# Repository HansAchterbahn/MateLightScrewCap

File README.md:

# MateLight-ScrewCap
This Repo is based on the idea of [MateLight](http://matelight.rocks/) and improves it by a screw cap which is easy to install and easy to remove from the coasters.

In this Repository you can find
- PCB schematics and board layouts created in Eagle,
- PCB Gerber data (ready for manufacturing),
- a 3D model of the PCB and
- a 3D model of the screw cap (for 3D printer).

Have also a look to the following Repos with Python Code for our MateLight for use with a Raspberry Pi:
- https://git.cccgoe.de/jugendgruppe/matelight-effects
- https://git.cccgoe.de/jugendgruppe/matelight
- https://git.cccgoe.de/jugendgruppe/ml_simulator

A small presentation about the PCB assembly process can be found here:
- https://jugendgruppe.cccgoe.de/reveal_js/00-MateLightScrewCapSoldering.html
- https://jugendgruppe.cccgoe.de/projekte/matelight.html

*Fork me and have fun!*

**MateLight of CCC youth group Göttingen at the 36c3 event 2019 in Leipzig**

## Power source

An APA102C LED consumes a maximum of 60 mA (red/green/blue each 20 mA). It is recommended to use a new 5 V / 1.4 mA power source for each 20 bottles(higher current delivery does not matter).

```
  ___  ^ 5V /    LED 1                            LED 19             LED 20             ___  ^ 5V /   LED 21
   |   | 1.4A  ___________  +5V            +5V   ___________  +5V    ___________ +5V     |   | 1.4A  ___________  +5V
   |   °------|    ___    |------         ------|    ___    |------|    ___    |--|      |   °------|    ___    |------
   |     GND  |   /   \   | GND            GND  |   /   \   | GND  |   /   \   | GND     |     GND  |   /   \   | GND
---°----------|  |     |  |------         ------|  |     |  |------|  |     |  |---------°----------|  |     |  |------
         CLK  |  |     |  | CLK     ...    CLK  |  |     |  | CLK  |  |     |  | CLK           CLK  |  |     |  | CLK     ...
------->------|  |     |  |------         ------|  |     |  |------|  |     |  |------------->------|  |     |  |------
         D    |   \___/   | D              D    |   \___/   | D    |   \___/   | D             D    |   \___/   | D
------->------|___________|------         ------|___________|------|___________|------------->------|___________|------
```

## 3D View (Fusion360)

Animated 3D STL model: [3d-model/MateLightScrewCap.stl](https://github.com/HansAchterbahn/MateLightScrewCap/blob/master/3d-model/MateLightScrewCap.stl)

__Top view__

__Bottom view__

## Schematic

## Board

__Top view__

__Bottom view__

## Manufacturing and assembly

__Manufactured PCBs__

__PCB with Cable__

__Manufactured screw caps__

__Assembled Mate bottle with PCB and screw cap__

__Assembled Mate bottle with PCB and screw cap lighting red__

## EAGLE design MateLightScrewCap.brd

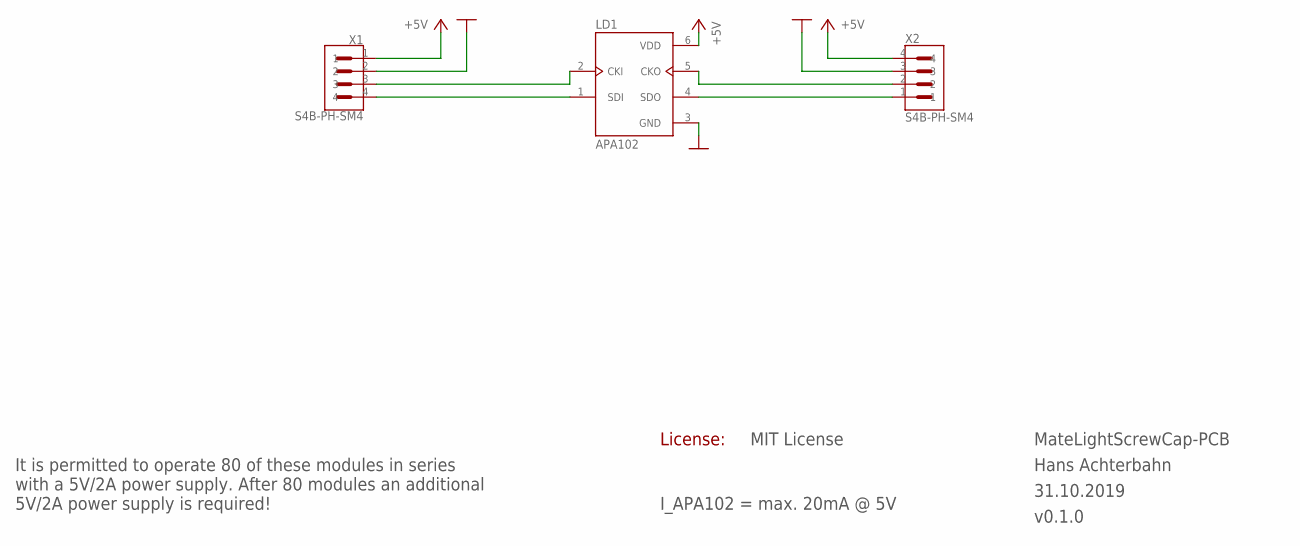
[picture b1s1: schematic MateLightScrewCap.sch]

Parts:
LD1: APA102; APA102C-5050
X1, X2: S4B-PH-SM4; JST_S4B-PH-SM4-TB

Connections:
+5V: LD1.6 (VDD), X1.1, X2.4
GND: LD1.3 (GND), X1.2, X2.3
LED-SPI-CLK-IN: LD1.2 (CKI), X1.3
LED-SPI-CLK-OUT: LD1.5 (CKO), X2.2
LED-SPI-MOSI-IN: LD1.1 (SDI), X1.4
LED-SPI-MOSI-OUT: LD1.4 (SDO), X2.1

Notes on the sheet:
I_APA102 = max. 20mA @ 5V
License:
It is permitted to operate 80 of these modules in series with a 5V/2A power supply. After 80 modules an additional 5V/2A power supply is required!

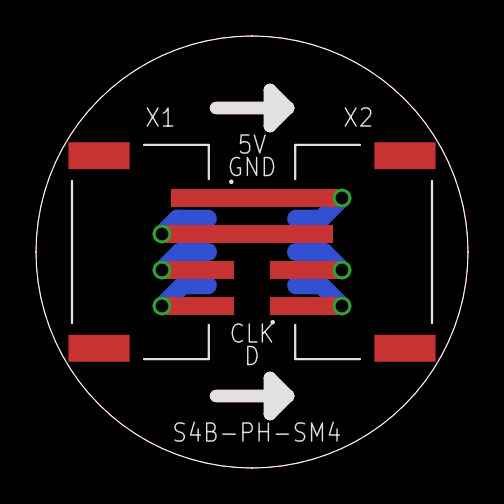
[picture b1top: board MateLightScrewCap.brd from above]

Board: 2 copper layers, 24.0 x 24.0 mm, 3 parts (1 on the bottom side), 6 nets.

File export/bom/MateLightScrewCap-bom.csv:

"Qty";"Value";"Device";"Package";"Parts";"Description";"DESCRIPTION";"DIGI-KEY";"MF";"MFN";"MOUSER";"RS-ONLINE";
"1";"APA102";"APA102APA102C-5050";"APA102C-5050";"LD1";"DotStar Micro LEDs (APA102–2020)- Smart SMD RGB LED - 100 pack";"";"";"";"";"";"";
"2";"S4B-PH-SM4";"S4B-PH-SM4-TB";"JST_S4B-PH-SM4-TB";"X1, X2";"JST - S4B-PH-SM4-TB";" Socket";" wire-board";" male";" PIN: 4";" 2mm";" SMT";

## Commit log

2019-10-31 Erster einfacher Prototyp fertig gestellt (Mit APA102 und Phoenix-1778780)
2019-11-01 Connector getauscht: Phoenix-1778780 → JST S4B-PH-SM4-TB
2019-11-01 3D Modell und Screenshots von 3D Modell hinzugefügt
2019-11-03 Konsistenzfehler behoben
2019-11-03 Doku geschrieben | Bilder für Doku hinzugefügt
2019-12-03 3D Modell der Schraubverschluss Kappe hinzugefügt
2019-12-12 Readme: Added section "Power source"
2019-12-12 Repaired document consistency | correct current source properties
2020-11-30 Doc: shorten pics names | added pic of 36c3

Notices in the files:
MateLightScrewCap.brd:
MIT License
MateLightScrewCap.sch:
LICENSE: MIT License
